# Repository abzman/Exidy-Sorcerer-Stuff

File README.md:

# Exidy-Sorcerer-Stuff
boards and maybe software for the exidy sorcerer

This repo currenly contains: 
* Non-exact replica of Howard Arington's four voice sound system
* SMD version of the above with provisions for all 8 bits of data
* Fairly close replica of Howard Arington's 2716 programmer
* Fairly close replica of ROM PAC PCB with mods based on RAM PAC description
* ROM PAC 'condom' to just not pass through pin 28 for modified sorcerers that have the /WR line there
  * This board also has a spot for a ribbon cable for expansion use to a cart switcher PCB
* Internal SRAM PCB that can replace any 16K bank of the sorcerer 1 or 2 up to 48K and can add an extra 8K up to 56K 

Upcoming boards:
* ROM PAC multi-port expander with jumpers for locating them in memory
* S100 card for connecting the sorcerer to a generic S100 chassis
* Exidy S100 Chassis replica PCB

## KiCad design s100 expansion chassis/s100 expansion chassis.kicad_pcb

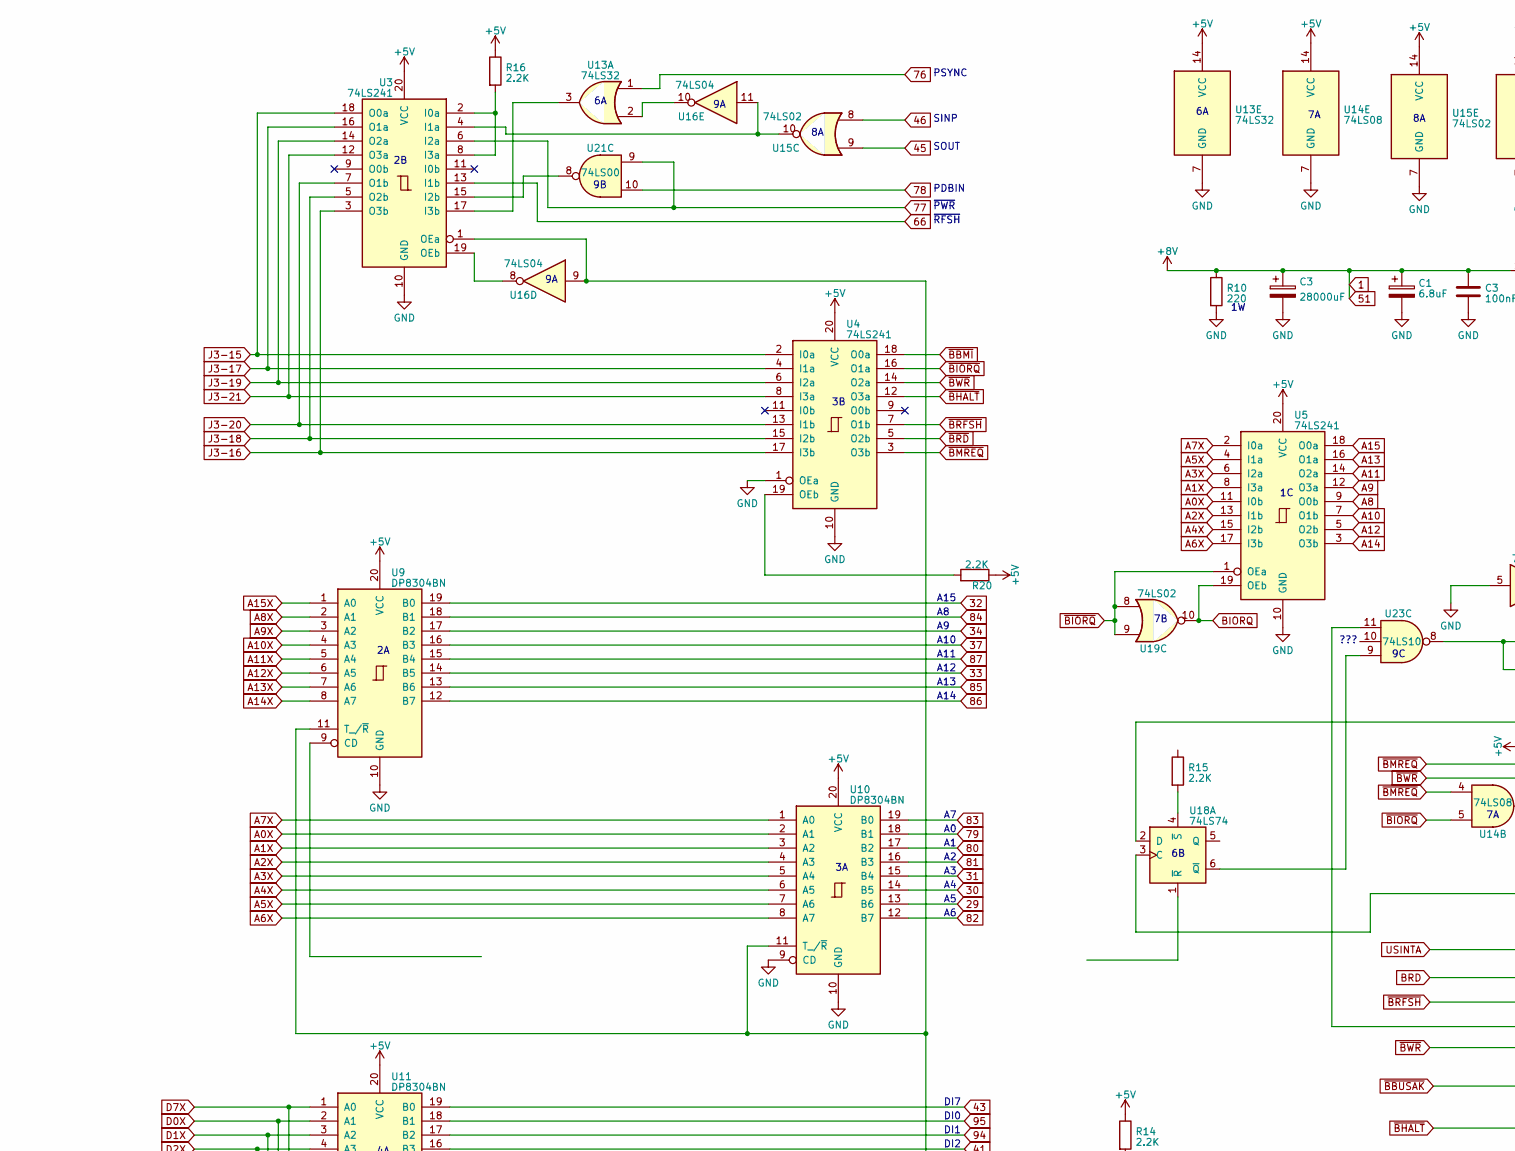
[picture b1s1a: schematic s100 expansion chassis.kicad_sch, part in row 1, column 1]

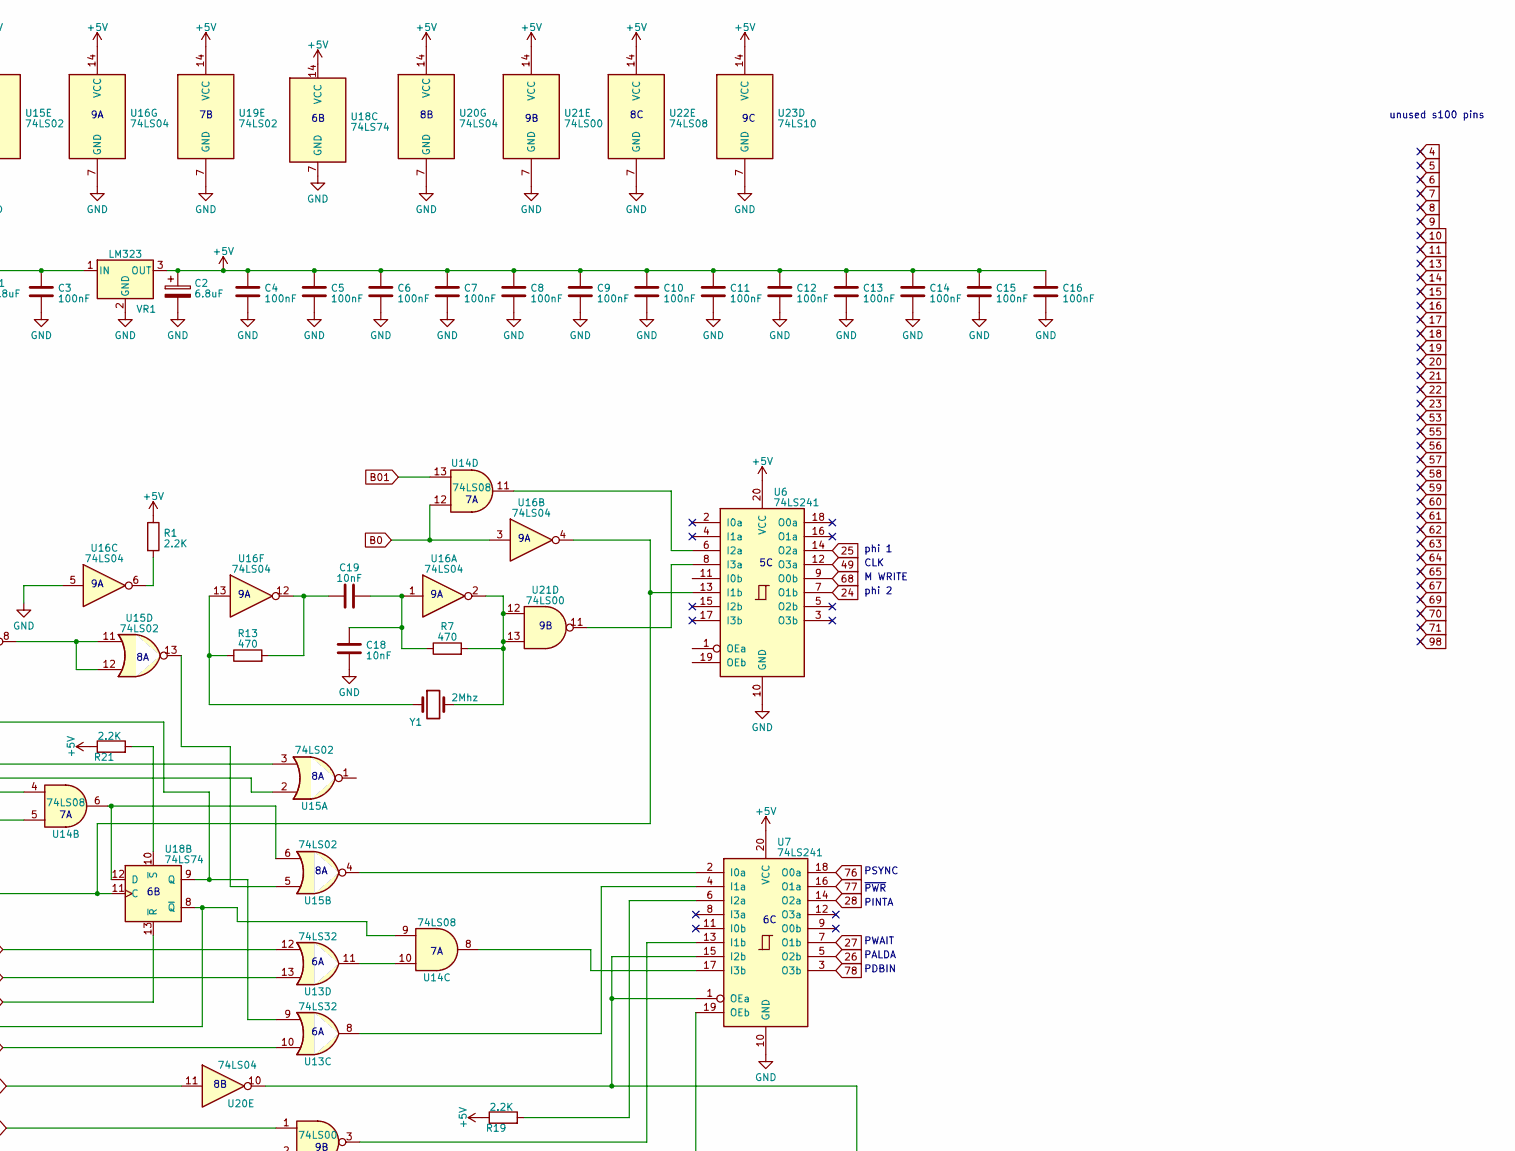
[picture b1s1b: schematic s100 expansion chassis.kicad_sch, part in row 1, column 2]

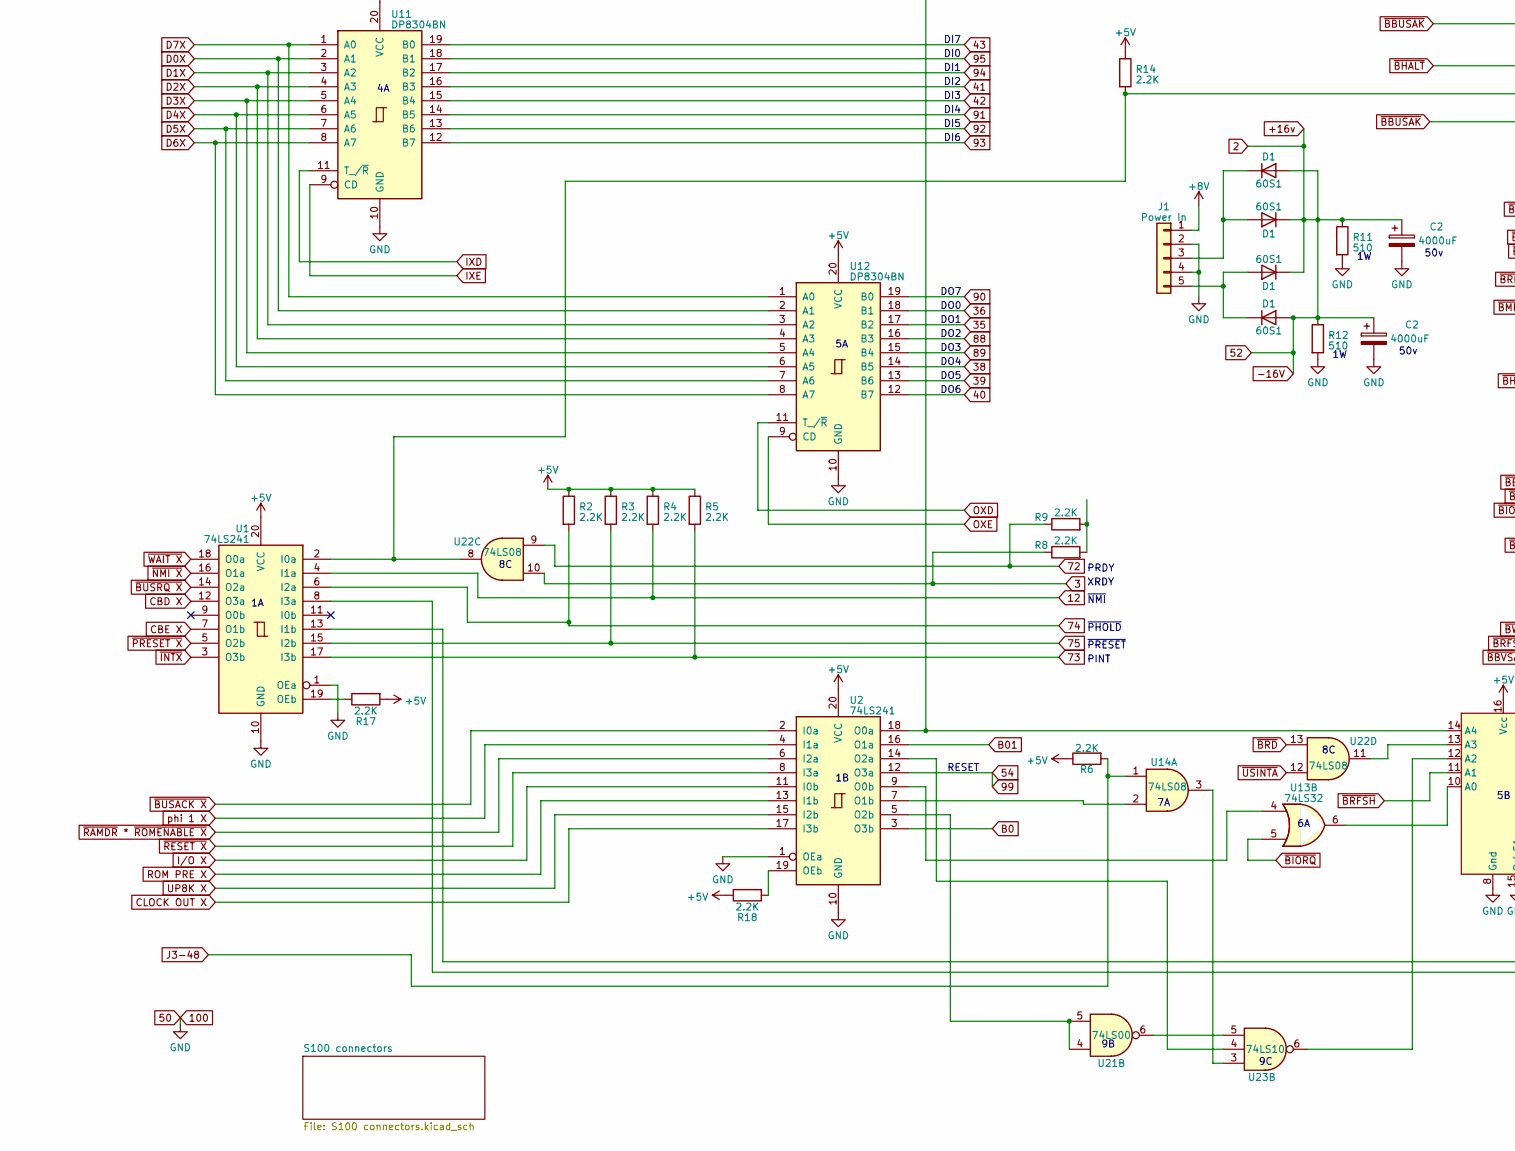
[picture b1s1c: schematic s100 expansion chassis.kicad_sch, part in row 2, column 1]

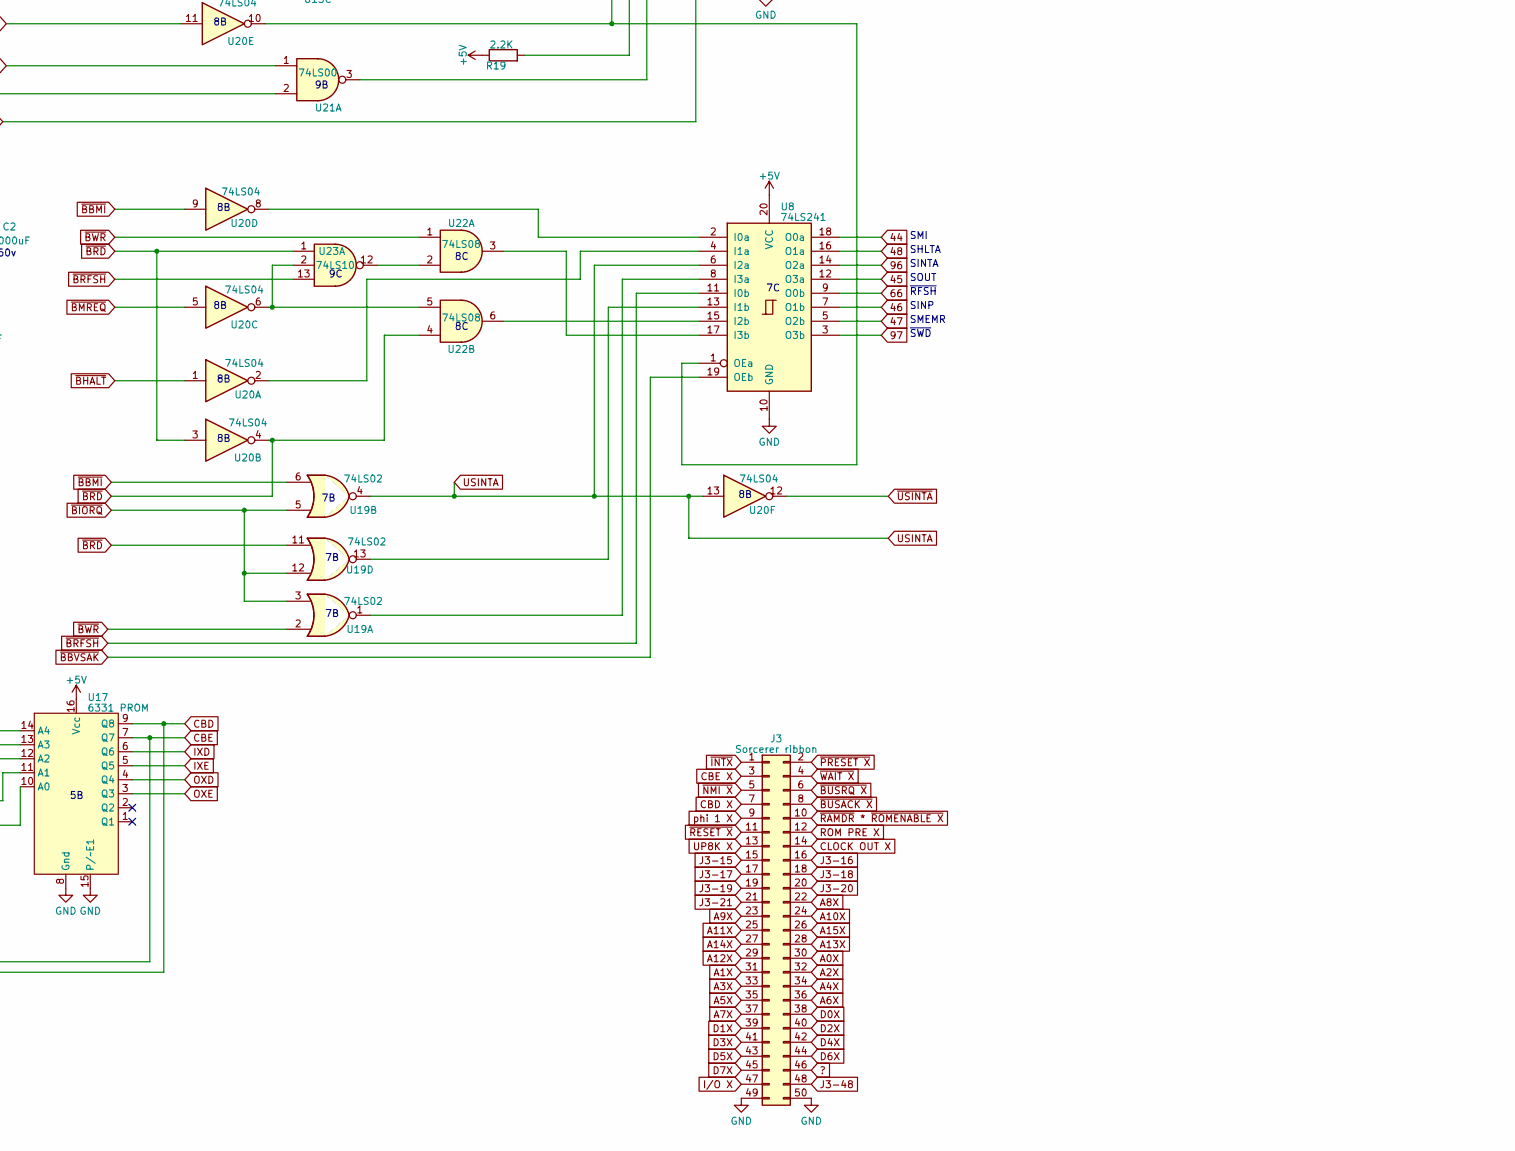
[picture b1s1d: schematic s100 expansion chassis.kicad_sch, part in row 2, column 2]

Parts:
C1: 6.8uF; CP_Radial_Tantal_D8.0mm_P5.00mm
C2: 4000uF; CP_Axial_L67.0mm_D23.0mm_P75.00mm_Horizontal
C3: 28000uF; CP_Radial_D35.0mm_P12.90mm_SnapIn
C4, C5, C6, C7, C8, C9, C10, C11, C12, C13, C14, C15, C16: 100nF; C_Disc_D6.0mm_W2.5mm_P6.35mm
C18, C19: 10nF; C_Disc_D6.0mm_W2.5mm_P6.35mm
D1: 60S1; D_DO-201AD_P15.24mm_Horizontal
J1: Power In; 5 pin inline molex 0.93
J3: Sorcerer ribbon; PinHeader_2x25_P2.54mm_Vertical
R1, R2, R3, R4, R5, R6, R8, R9, R14, R15, R16, R17, R18, R19, R20, R21: 2.2K; R_Axial_DIN0204_L3.6mm_D1.6mm_P12.7mm_Horizontal
R7, R13: 470; R_Axial_DIN0204_L3.6mm_D1.6mm_P12.7mm_Horizontal
R10: 220; R_Axial_DIN0204_L3.6mm_D1.6mm_P12.7mm_Horizontal
R11, R12: 510; R_Axial_DIN0204_L3.6mm_D1.6mm_P12.7mm_Horizontal
U1, U2, U3, U4, U5, U6, U7, U8: 74LS241; DIP-20_W7.62mm
U9, U10, U11, U12: DP8304BN; DIP-20_W7.62mm
U13: 74LS32; DIP-14_W7.62mm
U14, U22: 74LS08; DIP-14_W7.62mm
U15, U19: 74LS02; DIP-14_W7.62mm
U16, U20: 74LS04; DIP-14_W7.62mm
U17: 6331 PROM; DIP-16_W7.62mm
U18: 74LS74; DIP-14_W7.62mm
U21: 74LS00; DIP-14_W7.62mm
U23: 74LS10; DIP-14_W7.62mm
VR1: LM323; TO-3
Y1: 2Mhz; Crystal_HC33-U_Horizontal

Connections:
1: C1.1, C3.1, J1.1, R10.1, VR1.1 (IN); also elsewhere on the board
12: R4.2, U1.4 (I1a); also elsewhere on the board
24: U6.7 (O1b); also elsewhere on the board
25: U6.14 (O2a); also elsewhere on the board
26: U7.5 (O2b); also elsewhere on the board
27: U7.7 (O1b); also elsewhere on the board
28: U7.14 (O2a); also elsewhere on the board
29: U10.13 (B6); also elsewhere on the board
30: U10.14 (B5); also elsewhere on the board
31: U10.15 (B4); also elsewhere on the board
32: U9.19 (B0); also elsewhere on the board
33: U9.14 (B5); also elsewhere on the board
34: U9.17 (B2); also elsewhere on the board
35: U12.17 (B2); also elsewhere on the board
36: U12.18 (B1); also elsewhere on the board
37: U9.16 (B3); also elsewhere on the board
38: U12.14 (B5); also elsewhere on the board
39: U12.13 (B6); also elsewhere on the board
40: U12.12 (B7); also elsewhere on the board
41: U11.16 (B3); also elsewhere on the board
42: U11.15 (B4); also elsewhere on the board
43: U11.19 (B0); also elsewhere on the board
44: U8.18 (O0a); also elsewhere on the board
45: U8.12 (O3a), U15.9; also elsewhere on the board
46: U8.7 (O1b), U15.8; also elsewhere on the board
47: U8.5 (O2b); also elsewhere on the board
48: U8.16 (O1a); also elsewhere on the board
49: U6.12 (O3a); also elsewhere on the board
54: U2.12 (O3a); also elsewhere on the board
66: U3.13 (I1b), U8.9 (O0b); also elsewhere on the board
68: U6.9 (O0b); also elsewhere on the board
72: R9.1, U22.9; also elsewhere on the board
73: R5.2, U1.17 (I3b); also elsewhere on the board
74: R2.2, U1.6 (I2a); also elsewhere on the board
75: R3.2, U1.15 (I2b); also elsewhere on the board
76: U7.18 (O0a), U13.1; also elsewhere on the board
77: U3.6 (I2a), U7.16 (O1a), U21.9; also elsewhere on the board
78: U7.3 (O3b), U21.10; also elsewhere on the board
79: U10.18 (B1); also elsewhere on the board
80: U10.17 (B2); also elsewhere on the board
81: U10.16 (B3); also elsewhere on the board
82: U10.12 (B7); also elsewhere on the board
83: U10.19 (B0); also elsewhere on the board
84: U9.18 (B1); also elsewhere on the board
85: U9.13 (B6); also elsewhere on the board
86: U9.12 (B7); also elsewhere on the board
87: U9.15 (B4); also elsewhere on the board
88: U12.16 (B3); also elsewhere on the board
89: U12.15 (B4); also elsewhere on the board
90: U12.19 (B0); also elsewhere on the board
91: U11.14 (B5); also elsewhere on the board
92: U11.13 (B6); also elsewhere on the board
93: U11.12 (B7); also elsewhere on the board
94: U11.17 (B2); also elsewhere on the board
95: U11.18 (B1); also elsewhere on the board
96: U8.14 (O2a); also elsewhere on the board
97: U8.3 (O3b); also elsewhere on the board
?: J3.46
A0X: J3.30, U5.11 (I0b), U10.2 (A1)
A1X: J3.31, U5.8 (I3a), U10.3 (A2)
A2X: J3.32, U5.13 (I1b), U10.4 (A3)
A3X: J3.33, U5.6 (I2a), U10.5 (A4)
A4X: J3.34, U5.15 (I2b), U10.6 (A5)
A5X: J3.35, U5.4 (I1a), U10.7 (A6)
A6X: J3.36, U5.17 (I3b), U10.8 (A7)
A7X: J3.37, U5.2 (I0a), U10.1 (A0)
A8: U5.9 (O0b)
A8X: J3.22, U9.2 (A1)
A9: U5.12 (O3a)
A9X: J3.23, U9.3 (A2)
A10: U5.7 (O1b)
A10X: J3.24, U9.4 (A3)
A11: U5.14 (O2a)
A11X: J3.25, U9.5 (A4)
A12: U5.5 (O2b)
A12X: J3.29, U9.6 (A5)
A13: U5.16 (O1a)
A13X: J3.28, U9.7 (A6)
A14: U5.3 (O3b)
A14X: J3.27, U9.8 (A7)
A15: U5.18 (O0a)
A15X: J3.26, U9.1 (A0)
B0: U2.3 (O3b), U14.12, U16.3
B01: U2.16 (O1a), U14.13
BIORQ: U5.19 (OEb), U19.10
BRD: U13.13
CBD: U1.8 (I3a), U17.9 (Q8)
CBD X: J3.7, U1.12 (O3a)
CBE: U1.13 (I1b), U17.7 (Q7)
CBE X: J3.3, U1.7 (O1b)
CLOCK OUT X: J3.14, U2.17 (I3b)
D0X: J3.38, U11.2 (A1), U12.2 (A1)
D1X: J3.39, U11.3 (A2), U12.3 (A2)
D2X: J3.40, U11.4 (A3), U12.4 (A3)
D3X: J3.41, U11.5 (A4), U12.5 (A4)
D4X: J3.42, U11.6 (A5), U12.6 (A5)
D5X: J3.43, U11.7 (A6), U12.7 (A6)
D6X: J3.44, U11.8 (A7), U12.8 (A7)
D7X: J3.45, U11.1 (A0), U12.1 (A0)
IXD: U11.11 (T_/~R), U17.6 (Q6)
IXE: U11.9 (CD), U17.5 (Q5)
I/O X: J3.47, U2.11 (I0b)
J3-15: J3.15, U3.18 (O0a), U4.2 (I0a)
J3-16: J3.16, U3.3 (O3b), U4.17 (I3b)
J3-17: J3.17, U3.16 (O1a), U4.4 (I1a)
J3-18: J3.18, U3.5 (O2b), U4.15 (I2b)
J3-19: J3.19, U3.14 (O2a), U4.6 (I2a)
J3-20: J3.20, U3.7 (O1b), U4.13 (I1b)
J3-21: J3.21, U3.12 (O3a), U4.8 (I3a)
J3-48: J3.48, R6.2, U14.1
unnamed: C18.1, C19.2, R7.1, U16.1
unnamed: C19.1, R13.2, U16.12
unnamed: R1.2, U16.6
unnamed: R7.2, U16.2, U21.12, U21.13, Y1.2
unnamed: R8.2, R9.2
unnamed: R13.1, U16.13, Y1.1
unnamed: R14.2, U1.2 (I0a), U21.2, U22.8
unnamed: R17.1, U1.19 (OEb)
unnamed: U2.9 (O0b), U13.4
unnamed: U2.7 (O1b), U14.2
unnamed: U2.14 (O2a), U23.4
unnamed: U2.5 (O2b), U21.4, U21.5
unnamed: R18.2, U2.19 (OEb)
unnamed: R16.2, U3.2 (I0a), U3.8 (I3a)
unnamed: U3.4 (I1a), U15.10, U16.11
unnamed: U3.15 (I2b), U21.8
unnamed: U3.17 (I3b), U13.3
unnamed: U3.19 (OEb), U16.8
unnamed: R20.2, U4.19 (OEb)
unnamed: U6.6 (I2a), U14.11
unnamed: U6.8 (I3a), U21.11
unnamed: U7.2 (I0a), U15.4
unnamed: U7.4 (I1a), U13.8
unnamed: U7.13 (I1b), U21.3
unnamed: R19.2, U7.6 (I2a)
unnamed: U7.1 (OEa), U7.15 (I2b), U8.1 (OEa), U20.10
unnamed: U7.17 (I3b), U14.8
unnamed: U8.2 (I0a), U20.8
unnamed: U8.4 (I1a), U20.2
unnamed: U8.13 (I1b), U19.13
unnamed: U8.15 (I2b), U22.6
unnamed: U8.8 (I3a), U19.1
unnamed: U8.17 (I3b), U22.3
unnamed: U2.18 (O0a), U3.1 (OEa), U9.11 (T_/~R), U10.11 (T_/~R), U16.9, U17.14 (A4)
unnamed: U13.2, U16.10
unnamed: U13.11, U14.10
unnamed: U14.3, U23.3
unnamed: U15.11, U15.12, U23.8
unnamed: U15.5, U15.13
unnamed: U13.6, U17.10 (A0)
unnamed: U17.12 (A2), U23.6
unnamed: U17.13 (A3), U22.11
unnamed: U6.13 (I1b), U16.4, U18.3 (C), U18.11 (C)
unnamed: U13.9, U18.2 (D), U18.9 (Q)
unnamed: U18.6 (~Q), U23.9
unnamed: R15.2, U18.4 (~S)
unnamed: U14.6, U15.6, U18.12 (D)
unnamed: U14.9, U18.8 (~Q), U23.11
unnamed: R21.2, U18.10 (~S)
unnamed: U20.6, U22.5, U23.2
unnamed: U21.6, U23.5
unnamed: U22.2, U23.12
OXD: U12.11 (T_/~R), U17.4 (Q4)
OXE: U12.9 (CD), U17.3 (Q3)
ROM PRE X: J3.12, U2.13 (I1b)
UP8K X: J3.13, U2.15 (I2b)
USINTA: U8.6 (I2a), U13.12, U19.4, U20.13
phi 1 X: J3.9, U2.4 (I1a)
~BBMI: U4.18 (O0a), U19.6, U20.9
~BBUSAK: U7.19 (OEb), U20.11
~BBVSAK: U8.19 (OEb)
~BHALT: U4.12 (O3a), U20.1, U21.1
~BIORQ: U4.16 (O1a), U5.1 (OEa), U13.5, U14.5, U19.3, U19.5, U19.8, U19.9, U19.12
~BMREQ: U4.3 (O3b), U14.4, U15.3, U20.5
~BRD: U4.5 (O2b), U19.11, U20.3, U20.4, U22.4, U22.13, U23.1
~BRFSH: U4.7 (O1b), U8.11 (I0b), U17.11 (A1), U18.13 (~R), U23.13
~BUSACK X: J3.8, U2.2 (I0a)
~BUSRQ X: J3.6, U1.14 (O2a)
~BWR: U4.14 (O2a), U13.10, U15.2, U19.2, U22.1
~INTX: J3.1, U1.3 (O3b)
~NMI X: J3.5, U1.16 (O1a)
~PRESET X: J3.2, U1.5 (O2b)
~RAMDR * ~ROMENABLE X: J3.10, U2.6 (I2a)
~RESET X: J3.11, U2.8 (I3a)
~USINTA: U20.12, U22.12
~WAIT X: J3.4, U1.18 (O0a)

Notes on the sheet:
SOUT
A11
XRDY
DO3
PINT
DO0
SMEMR
DO7
~{RFSH}
DI5
PDBIN
phi 2
PALDA
phi 1
A10
DI7
DI4
DI6
DO6
M WRITE
~{PWR}
SINTA
A12
PINTA
A14
DI3
SINP
SHLTA
DO5
unused s100 pins
DI0
~{NMI}
PSYNC
~{PRESET}
SMI
DI1
A13
DO2
DO4
PRDY

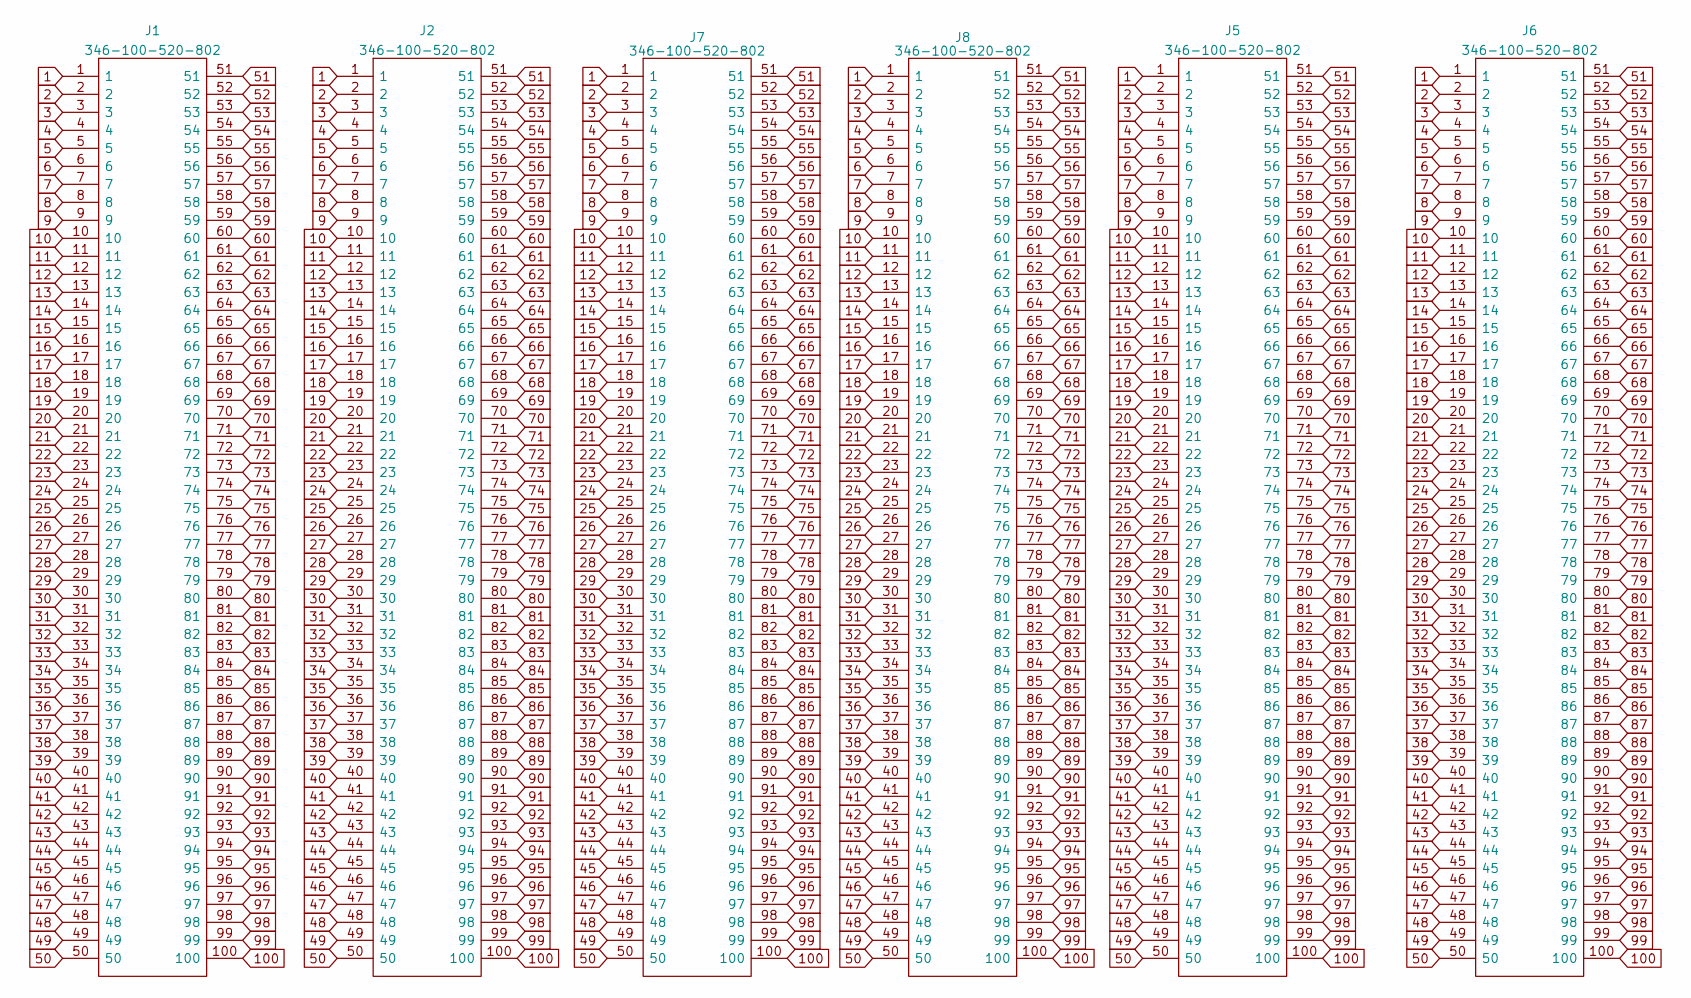
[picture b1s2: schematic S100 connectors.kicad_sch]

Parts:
J1, J2, J5, J6, J7, J8: 346-100-520-802; 346100520802; Mouser Part Number 587-346-100-520-802

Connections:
1: J1.1, J1.51, J2.1, J2.51, J5.1, J5.51, J6.1, J6.51, J7.1, J7.51, J8.1, J8.51; also elsewhere on the board
6: J1.6, J2.6, J5.6, J6.6, J7.6, J8.6
7: J1.7, J2.7, J5.7, J6.7, J7.7, J8.7
8: J1.8, J2.8, J5.8, J6.8, J7.8, J8.8
9: J1.9, J2.9, J5.9, J6.9, J7.9, J8.9
10: J1.10, J2.10, J5.10, J6.10, J7.10, J8.10
11: J1.11, J2.11, J5.11, J6.11, J7.11, J8.11
12: J1.12, J2.12, J5.12, J6.12, J7.12, J8.12; also elsewhere on the board
13: J1.13, J2.13, J5.13, J6.13, J7.13, J8.13
14: J1.14, J2.14, J5.14, J6.14, J7.14, J8.14
15: J1.15, J2.15, J5.15, J6.15, J7.15, J8.15
16: J1.16, J2.16, J5.16, J6.16, J7.16, J8.16
17: J1.17, J2.17, J5.17, J6.17, J7.17, J8.17
18: J1.18, J2.18, J5.18, J6.18, J7.18, J8.18
19: J1.19, J2.19, J5.19, J6.19, J7.19, J8.19
20: J1.20, J2.20, J5.20, J6.20, J7.20, J8.20
21: J1.21, J2.21, J5.21, J6.21, J7.21, J8.21
22: J1.22, J2.22, J5.22, J6.22, J7.22, J8.22
23: J1.23, J2.23, J5.23, J6.23, J7.23, J8.23
24: J1.24, J2.24, J5.24, J6.24, J7.24, J8.24; also elsewhere on the board
25: J1.25, J2.25, J5.25, J6.25, J7.25, J8.25; also elsewhere on the board
26: J1.26, J2.26, J5.26, J6.26, J7.26, J8.26; also elsewhere on the board
27: J1.27, J2.27, J5.27, J6.27, J7.27, J8.27; also elsewhere on the board
28: J1.28, J2.28, J5.28, J6.28, J7.28, J8.28; also elsewhere on the board
29: J1.29, J2.29, J5.29, J6.29, J7.29, J8.29; also elsewhere on the board
30: J1.30, J2.30, J5.30, J6.30, J7.30, J8.30; also elsewhere on the board
31: J1.31, J2.31, J5.31, J6.31, J7.31, J8.31; also elsewhere on the board
32: J1.32, J2.32, J5.32, J6.32, J7.32, J8.32; also elsewhere on the board
33: J1.33, J2.33, J5.33, J6.33, J7.33, J8.33; also elsewhere on the board
34: J1.34, J2.34, J5.34, J6.34, J7.34, J8.34; also elsewhere on the board
35: J1.35, J2.35, J5.35, J6.35, J7.35, J8.35; also elsewhere on the board
36: J1.36, J2.36, J5.36, J6.36, J7.36, J8.36; also elsewhere on the board
37: J1.37, J2.37, J5.37, J6.37, J7.37, J8.37; also elsewhere on the board
38: J1.38, J2.38, J5.38, J6.38, J7.38, J8.38; also elsewhere on the board
39: J1.39, J2.39, J5.39, J6.39, J7.39, J8.39; also elsewhere on the board
40: J1.40, J2.40, J5.40, J6.40, J7.40, J8.40; also elsewhere on the board
41: J1.41, J2.41, J5.41, J6.41, J7.41, J8.41; also elsewhere on the board
42: J1.42, J2.42, J5.42, J6.42, J7.42, J8.42; also elsewhere on the board
43: J1.43, J2.43, J5.43, J6.43, J7.43, J8.43; also elsewhere on the board
44: J1.44, J2.44, J5.44, J6.44, J7.44, J8.44; also elsewhere on the board
45: J1.45, J2.45, J5.45, J6.45, J7.45, J8.45; also elsewhere on the board
46: J1.46, J2.46, J5.46, J6.46, J7.46, J8.46; also elsewhere on the board
47: J1.47, J2.47, J5.47, J6.47, J7.47, J8.47; also elsewhere on the board
48: J1.48, J2.48, J5.48, J6.48, J7.48, J8.48; also elsewhere on the board
49: J1.49, J2.49, J5.49, J6.49, J7.49, J8.49; also elsewhere on the board
53: J1.53, J2.53, J5.53, J6.53, J7.53, J8.53
54: J1.54, J1.99, J2.54, J2.99, J5.54, J5.99, J6.54, J6.99, J7.54, J7.99, J8.54, J8.99; also elsewhere on the board
55: J1.55, J2.55, J5.55, J6.55, J7.55, J8.55
56: J1.56, J2.56, J5.56, J6.56, J7.56, J8.56
57: J1.57, J2.57, J5.57, J6.57, J7.57, J8.57
58: J1.58, J2.58, J5.58, J6.58, J7.58, J8.58
59: J1.59, J2.59, J5.59, J6.59, J7.59, J8.59
60: J1.60, J2.60, J5.60, J6.60, J7.60, J8.60
61: J1.61, J2.61, J5.61, J6.61, J7.61, J8.61
62: J1.62, J2.62, J5.62, J6.62, J7.62, J8.62
63: J1.63, J2.63, J5.63, J6.63, J7.63, J8.63
64: J1.64, J2.64, J5.64, J6.64, J7.64, J8.64
65: J1.65, J2.65, J5.65, J6.65, J7.65, J8.65
66: J1.66, J2.66, J5.66, J6.66, J7.66, J8.66; also elsewhere on the board
67: J1.67, J2.67, J5.67, J6.67, J7.67, J8.67
68: J1.68, J2.68, J5.68, J6.68, J7.68, J8.68; also elsewhere on the board
69: J1.69, J2.69, J5.69, J6.69, J7.69, J8.69
70: J1.70, J2.70, J5.70, J6.70, J7.70, J8.70
71: J1.71, J2.71, J5.71, J6.71, J7.71, J8.71
72: J1.72, J2.72, J5.72, J6.72, J7.72, J8.72; also elsewhere on the board
73: J1.73, J2.73, J5.73, J6.73, J7.73, J8.73; also elsewhere on the board
74: J1.74, J2.74, J5.74, J6.74, J7.74, J8.74; also elsewhere on the board
75: J1.75, J2.75, J5.75, J6.75, J7.75, J8.75; also elsewhere on the board
76: J1.76, J2.76, J5.76, J6.76, J7.76, J8.76; also elsewhere on the board
77: J1.77, J2.77, J5.77, J6.77, J7.77, J8.77; also elsewhere on the board
78: J1.78, J2.78, J5.78, J6.78, J7.78, J8.78; also elsewhere on the board
79: J1.79, J2.79, J5.79, J6.79, J7.79, J8.79; also elsewhere on the board
80: J1.80, J2.80, J5.80, J6.80, J7.80, J8.80; also elsewhere on the board
81: J1.81, J2.81, J5.81, J6.81, J7.81, J8.81; also elsewhere on the board
82: J1.82, J2.82, J5.82, J6.82, J7.82, J8.82; also elsewhere on the board
83: J1.83, J2.83, J5.83, J6.83, J7.83, J8.83; also elsewhere on the board
84: J1.84, J2.84, J5.84, J6.84, J7.84, J8.84; also elsewhere on the board
85: J1.85, J2.85, J5.85, J6.85, J7.85, J8.85; also elsewhere on the board
86: J1.86, J2.86, J5.86, J6.86, J7.86, J8.86; also elsewhere on the board
87: J1.87, J2.87, J5.87, J6.87, J7.87, J8.87; also elsewhere on the board
88: J1.88, J2.88, J5.88, J6.88, J7.88, J8.88; also elsewhere on the board
89: J1.89, J2.89, J5.89, J6.89, J7.89, J8.89; also elsewhere on the board
90: J1.90, J2.90, J5.90, J6.90, J7.90, J8.90; also elsewhere on the board
91: J1.91, J2.91, J5.91, J6.91, J7.91, J8.91; also elsewhere on the board
92: J1.92, J2.92, J5.92, J6.92, J7.92, J8.92; also elsewhere on the board
93: J1.93, J2.93, J5.93, J6.93, J7.93, J8.93; also elsewhere on the board
94: J1.94, J2.94, J5.94, J6.94, J7.94, J8.94; also elsewhere on the board
95: J1.95, J2.95, J5.95, J6.95, J7.95, J8.95; also elsewhere on the board
96: J1.96, J2.96, J5.96, J6.96, J7.96, J8.96; also elsewhere on the board
97: J1.97, J2.97, J5.97, J6.97, J7.97, J8.97; also elsewhere on the board
98: J1.98, J2.98, J5.98, J6.98, J7.98, J8.98

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
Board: 2 copper layers, 79 parts (0 on the bottom side), 217 nets, no tracks yet.

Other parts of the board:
C17: 28000uF; CP_Radial_D35.0mm_P12.90mm_SnapIn
C21, C22: 4000uF; CP_Axial_L67.0mm_D23.0mm_P75.00mm_Horizontal
CR1, CR2, CR3, CR4: 60S1; D_DO-201AD_P15.24mm_Horizontal
J4: Power In; 5 pin inline molex 0.93

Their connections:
1: C17.1, J4.1; also elsewhere on the board

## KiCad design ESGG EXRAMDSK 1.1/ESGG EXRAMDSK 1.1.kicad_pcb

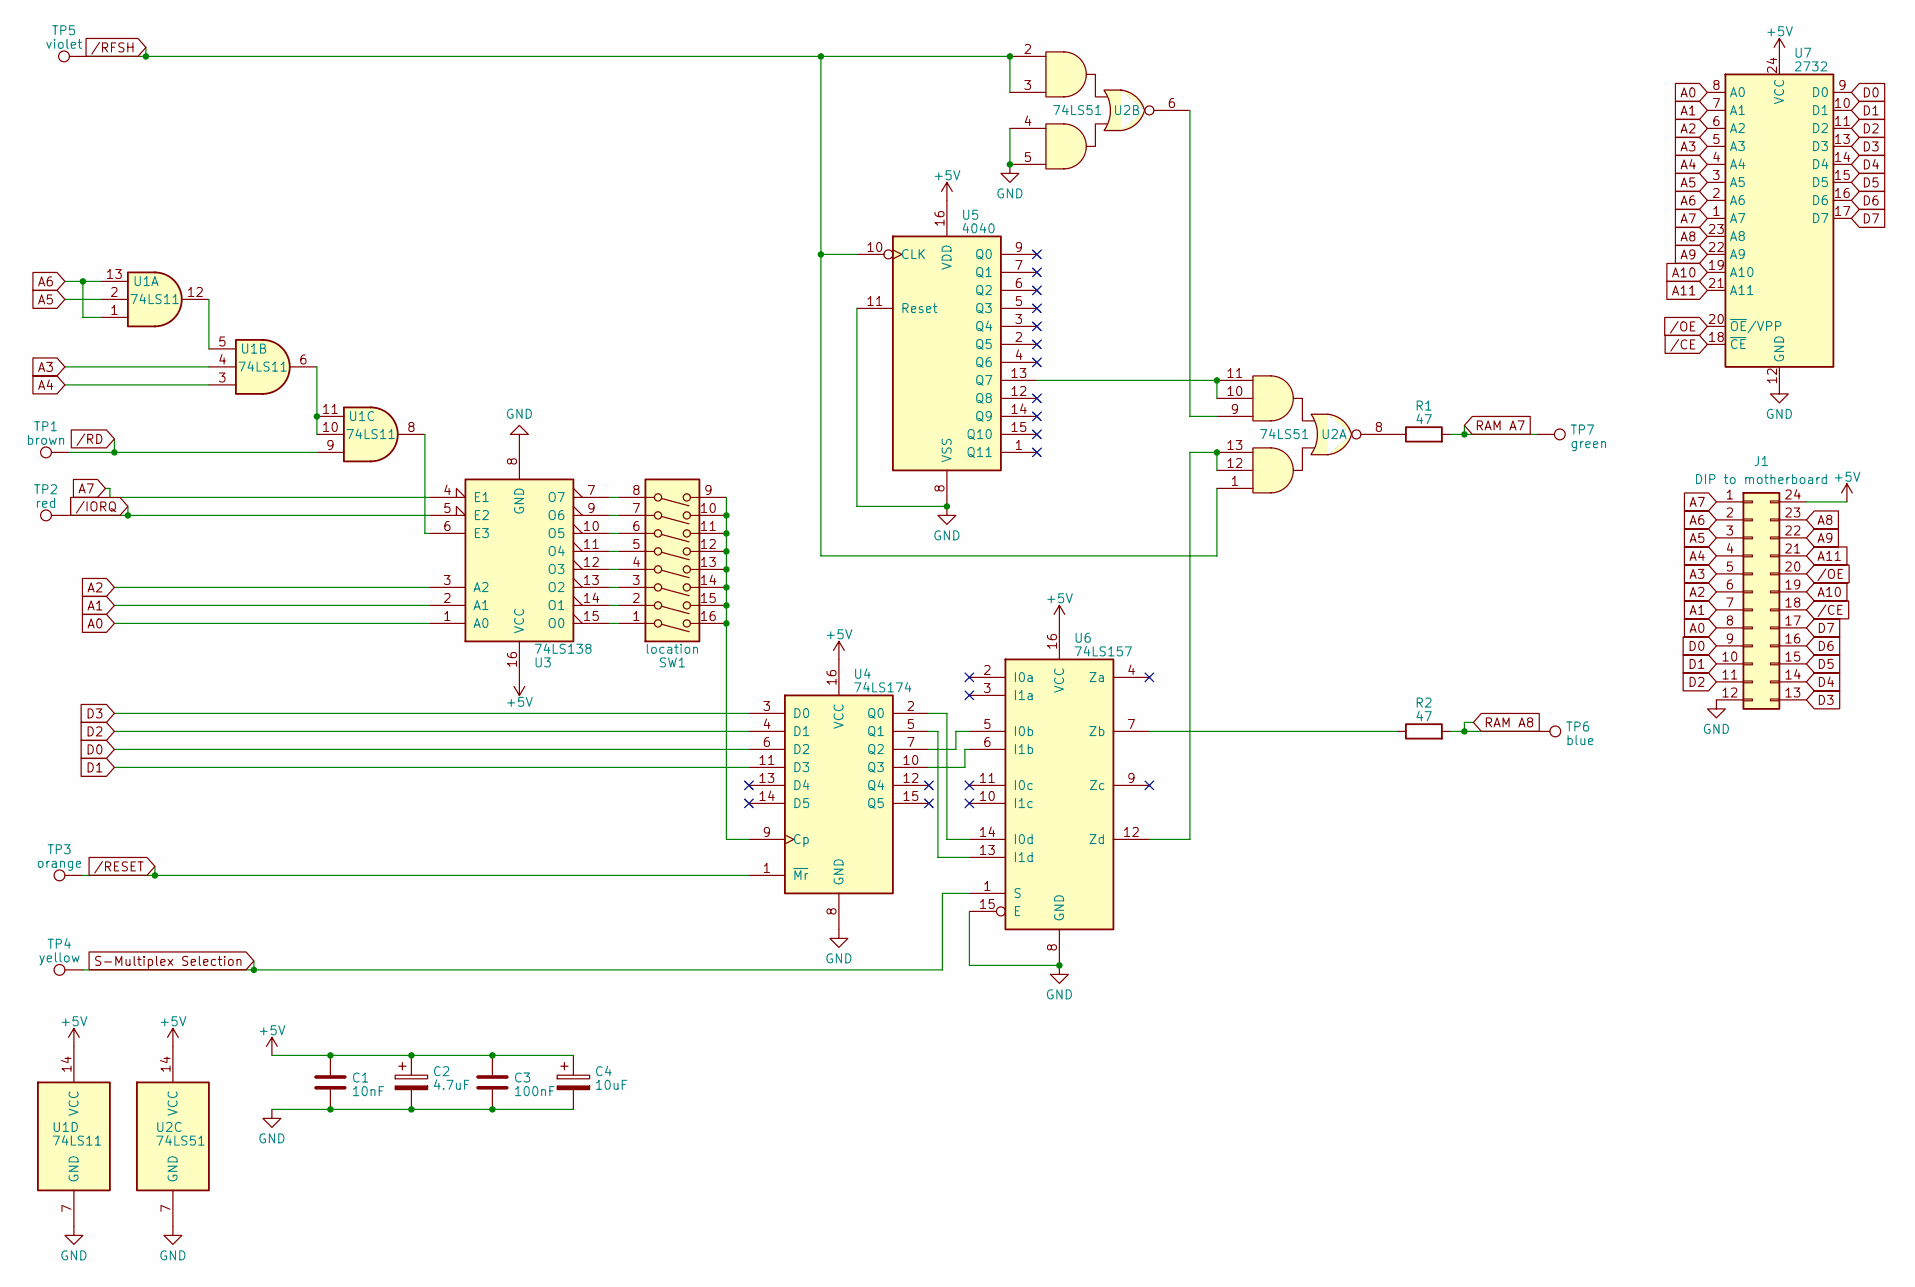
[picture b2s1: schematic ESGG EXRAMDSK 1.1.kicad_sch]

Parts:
C1: 10nF; C_Disc_D4.3mm_W1.9mm_P5.00mm
C2: 4.7uF; C_Disc_D4.3mm_W1.9mm_P5.00mm
C3: 100nF; C_Disc_D4.3mm_W1.9mm_P5.00mm
C4: 10uF; C_Axial_L12.0mm_D6.5mm_P20.00mm_Horizontal
J1: DIP to motherboard; DIP-24_W15.24mm
R1, R2: 47; R_Axial_DIN0207_L6.3mm_D2.5mm_P10.16mm_Horizontal
SW1: location; SW_DIP_SPSTx08_Slide_9.78x22.5mm_W7.62mm_P2.54mm
TP1: brown; TestPoint_Plated_Hole_D2.0mm
TP2: red; TestPoint_Plated_Hole_D2.0mm
TP3: orange; TestPoint_Plated_Hole_D2.0mm
TP4: yellow; TestPoint_Plated_Hole_D2.0mm
TP5: violet; TestPoint_Plated_Hole_D2.0mm
TP6: blue; TestPoint_Plated_Hole_D2.0mm
TP7: green; TestPoint_Plated_Hole_D2.0mm
U1: 74LS11; DIP-14_W7.62mm
U2: 74LS51; DIP-14_W7.62mm
U3: 74LS138; DIP-16_W7.62mm
U4: 74LS174; DIP-16_W7.62mm
U5: 4040; DIP-16_W7.62mm
U6: 74LS157; DIP-16_W7.62mm
U7: 2732; DIP-24_W15.24mm

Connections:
+5V: C1.1, C2.1, C3.1, C4.1, J1.24, U1.14 (VCC), U2.14 (VCC), U3.16 (VCC), U4.16 (VCC), U5.16 (VDD), U6.16 (VCC), U7.24 (VCC)
A0: J1.8, U3.1 (A0), U7.8 (A0)
A1: J1.7, U3.2 (A1), U7.7 (A1)
A2: J1.6, U3.3 (A2), U7.6 (A2)
A3: J1.5, U1.4, U7.5 (A3)
A4: J1.4, U1.3, U7.4 (A4)
A5: J1.3, U1.2, U7.3 (A5)
A6: J1.2, U1.1, U1.13, U7.2 (A6)
A7: J1.1, U3.4 (E1), U7.1 (A7)
A8: J1.23, U7.23 (A8)
A9: J1.22, U7.22 (A9)
A10: J1.19, U7.19 (A10)
A11: J1.21, U7.21 (A11)
D0: J1.9, U4.6 (D2), U7.9 (D0)
D1: J1.10, U4.11 (D3), U7.10 (D1)
D2: J1.11, U4.4 (D1), U7.11 (D2)
D3: J1.13, U4.3 (D0), U7.13 (D3)
D4: J1.14, U7.14 (D4)
D5: J1.15, U7.15 (D5)
D6: J1.16, U7.16 (D6)
D7: J1.17, U7.17 (D7)
GND: C1.2, C2.2, C3.2, C4.2, J1.12, U1.7 (GND), U2.4, U2.5, U2.7 (GND), U3.8 (GND), U4.8 (GND), U5.8 (VSS), U5.11 (Reset), U6.8 (GND), U6.15 (E), U7.12 (GND)
unnamed: R1.1, U2.8
unnamed: U1.6, U1.10, U1.11
unnamed: U1.5, U1.12
unnamed: U2.6, U2.9
unnamed: U1.8, U3.6 (E3)
unnamed: SW1.1, U3.15 (O0)
unnamed: SW1.2, U3.14 (O1)
unnamed: SW1.3, U3.13 (O2)
unnamed: SW1.4, U3.12 (O3)
unnamed: SW1.5, U3.11 (O4)
unnamed: SW1.6, U3.10 (O5)
unnamed: SW1.7, U3.9 (O6)
unnamed: SW1.8, U3.7 (O7)
unnamed: SW1.9, SW1.10, SW1.11, SW1.12, SW1.13, SW1.14, SW1.15, SW1.16, U4.9 (Cp)
unnamed: U4.2 (Q0), U6.14 (I0d)
unnamed: U4.5 (Q1), U6.13 (I1d)
unnamed: U4.7 (Q2), U6.5 (I0b)
unnamed: U4.10 (Q3), U6.6 (I1b)
unnamed: U2.10, U2.11, U5.13 (Q7)
unnamed: R2.1, U6.7 (Zb)
unnamed: U2.12, U2.13, U6.12 (Zd)
RAM A7: R1.2, TP7.1
RAM A8: R2.2, TP6.1
S-Multiplex Selection: TP4.1, U6.1 (S)
/CE: J1.18, U7.18 (~CE)
/IORQ: TP2.1, U3.5 (E2)
/OE: J1.20, U7.20 (~OE/VPP)
/RD: TP1.1, U1.9
/RESET: TP3.1, U4.1 (~Mr)
/RFSH: TP5.1, U2.1, U2.2, U2.3, U5.10 (CLK)

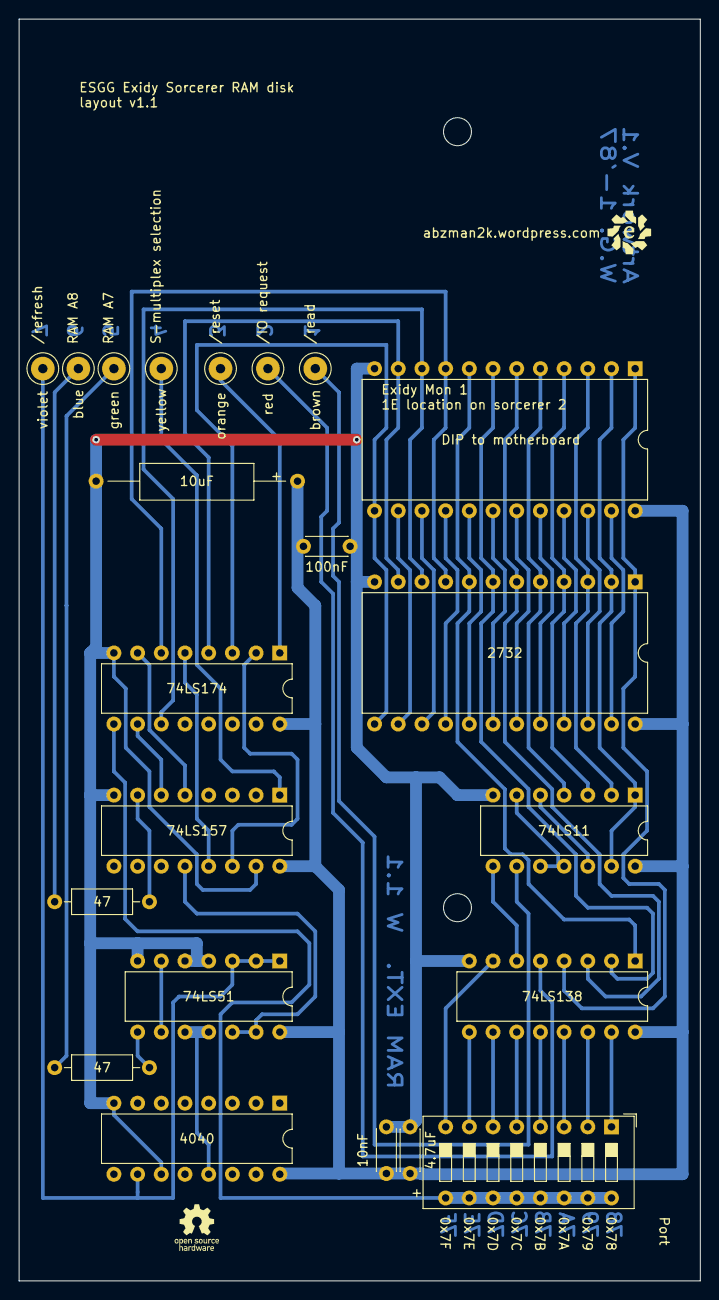
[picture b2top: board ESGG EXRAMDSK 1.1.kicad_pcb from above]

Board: 2 copper layers, 73.0 x 135.3 mm, 22 parts (0 on the bottom side), 52 nets.
